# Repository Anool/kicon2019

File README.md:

# kicon2019
FreeCAD tutorial and workshop at KiCon 2019, Chicago

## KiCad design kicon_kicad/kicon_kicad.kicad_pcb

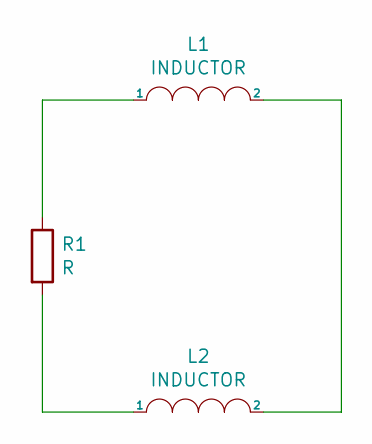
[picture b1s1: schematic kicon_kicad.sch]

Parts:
L1: INDUCTOR; inductor_1
L2: INDUCTOR; inductor_2
R1: R; R_Axial_DIN0207_L6.3mm_D2.5mm_P10.16mm_Horizontal

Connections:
unnamed: L1.1, R1.1
unnamed: L1.2, L2.2
unnamed: L2.1, R1.2

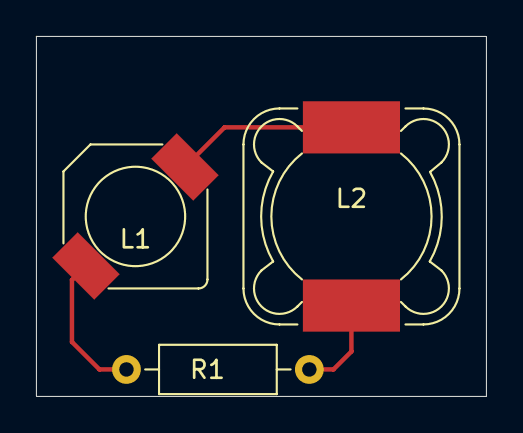
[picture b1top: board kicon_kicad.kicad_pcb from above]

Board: 2 copper layers, 25.0 x 20.0 mm, 3 parts (0 on the bottom side), 3 nets.

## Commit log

2019-02-19 added links
2019-02-19 removed large ZIP file
2019-02-19 added files
2019-03-07 modified resistor
2019-03-07 added Wurth inductor data
2019-03-11 modified inductor
2019-04-29 updated slide deck
